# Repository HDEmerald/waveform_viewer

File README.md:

# waveform_viewer
A guitar pedal whose sole purpose is to display the guitar's signal onto a display.

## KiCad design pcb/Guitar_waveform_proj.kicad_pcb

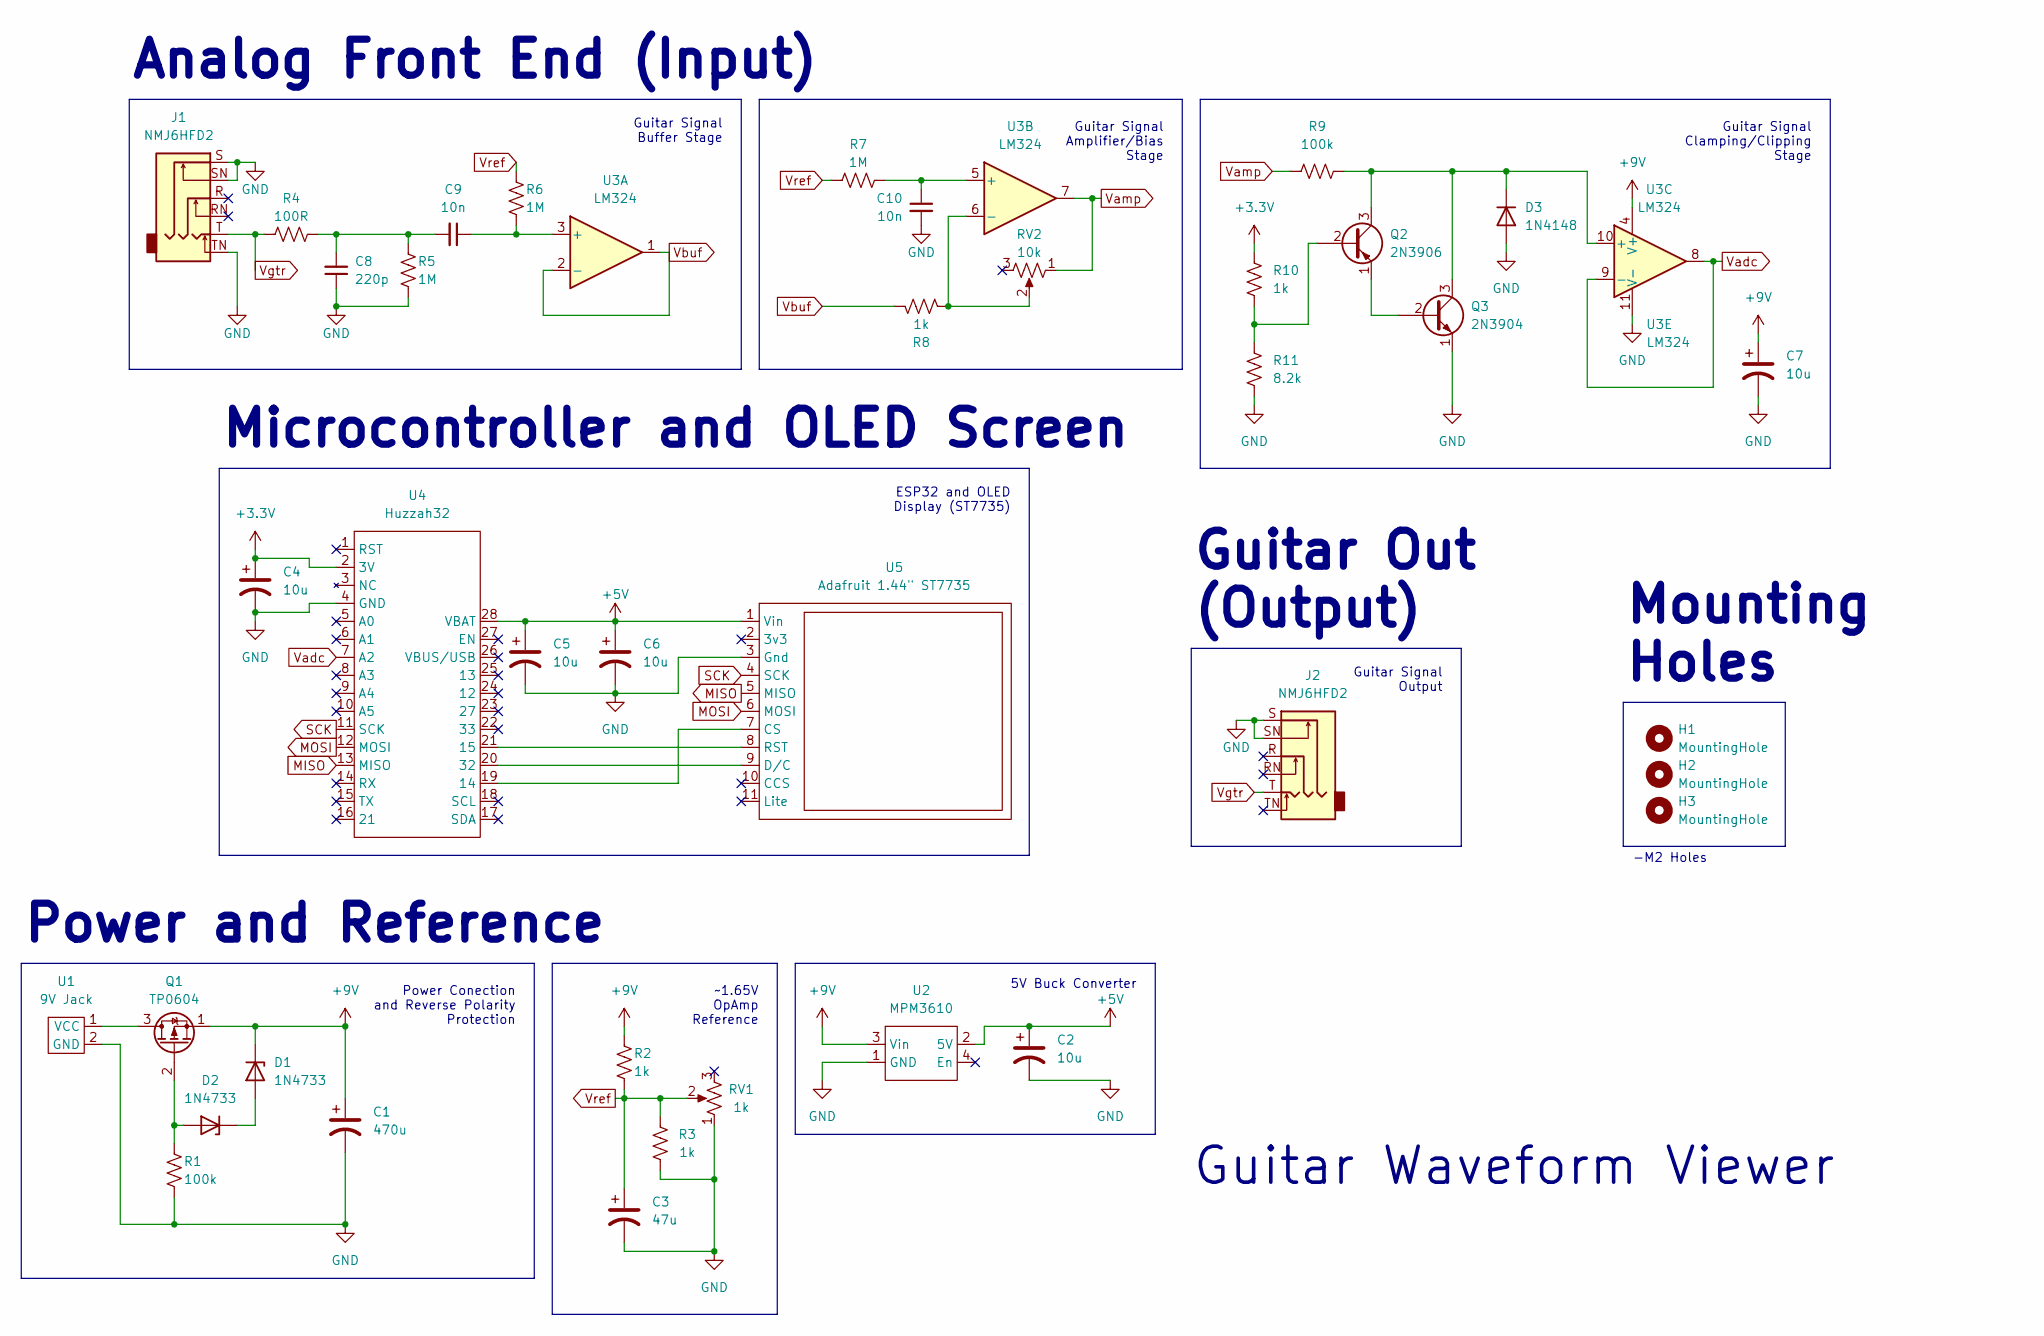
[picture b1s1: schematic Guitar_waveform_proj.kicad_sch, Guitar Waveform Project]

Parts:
C1: 470u; CP_Radial_D8.0mm_P3.50mm
C2, C4, C5, C6, C7: 10u; CP_Radial_D4.0mm_P1.50mm
C3: 47u; CP_Radial_D5.0mm_P2.00mm
C8: 220p; C_Disc_D5.1mm_W3.2mm_P5.00mm
C9, C10: 10n; C_Disc_D5.1mm_W3.2mm_P5.00mm
D1, D2: 1N4733; D_DO-41_SOD81_P7.62mm_Horizontal
D3: 1N4148; D_DO-35_SOD27_P7.62mm_Horizontal
H1, H2, H3: MountingHole; MountingHole_2.2mm_M2
J1, J2: NMJ6HFD2; My Guitar Jack
Q1: TP0604; TO-92_Inline_Wide
Q2: 2N3906; TO-92_Inline_Wide
Q3: 2N3904; TO-92_Inline_Wide
R1, R9: 100k; R_Axial_DIN0207_L6.3mm_D2.5mm_P10.16mm_Horizontal
R2, R3, R8, R10: 1k; R_Axial_DIN0207_L6.3mm_D2.5mm_P10.16mm_Horizontal
R4: 100R; R_Axial_DIN0207_L6.3mm_D2.5mm_P10.16mm_Horizontal
R5, R6, R7: 1M; R_Axial_DIN0207_L6.3mm_D2.5mm_P10.16mm_Horizontal
R11: 8.2k; R_Axial_DIN0207_L6.3mm_D2.5mm_P10.16mm_Horizontal
RV1: 1k; PinHeader_1x03_P2.54mm_Vertical
RV2: 10k; PinHeader_1x03_P2.54mm_Vertical
U1: 9V Jack; PinHeader_1x02_P2.54mm_Vertical
U2: MPM3610; PinHeader_1x04_P2.54mm_Vertical
U3: LM324; DIP-14_W7.62mm_LongPads
U4: Huzzah32; Adafruit_Huzzah32
U5: Adafruit 1.44" ST7735; Adafruit_1.44_ST7735

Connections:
+3.3V: C4.1, R10.1, U4.2 (3V)
+5V: C2.1, C5.1, C6.1, U2.2 (5V), U4.28 (VBAT), U5.1 (Vin)
+9V: C1.1, C7.1, D1.1 (K), Q1.1 (S), R2.1, U2.3 (Vin), U3.4 (V+)
GND: C1.2, C2.2, C3.2, C4.2, C5.2, C6.2, C7.2, C8.1, C10.2, D3.2 (A), J1.S, J1.SN, J1.TN, J2.S, J2.SN, Q3.1 (E), R1.2, R3.2, R5.2, R11.2, RV1.1, U1.2 (GND), U2.1 (GND), U3.11 (V-), U4.4 (GND), U5.3 (Gnd)
MISO: U4.13 (MISO), U5.5 (MISO)
MOSI: U4.12 (MOSI), U5.6 (MOSI)
unnamed: C8.2, C9.2, R4.1, R5.1
unnamed: D1.2 (A), D2.1 (K)
unnamed: D2.2 (A), Q1.2 (G), R1.1
unnamed: D3.1 (K), Q2.3 (C), Q3.3 (C), R9.1, U3.10 (+)
unnamed: Q1.3 (D), U1.1 (VCC)
unnamed: Q2.2 (B), R10.2, R11.1
unnamed: Q2.1 (E), Q3.2 (B)
unnamed: C9.1, R6.2, U3.3 (+)
unnamed: C10.1, R7.1, U3.5 (+)
unnamed: R8.1, RV2.2, U3.6 (-)
unnamed: U4.19 (14), U5.7 (CS)
unnamed: U4.21 (15), U5.8 (RST)
unnamed: U4.20 (32), U5.9 (D/C)
SCK: U4.11 (SCK), U5.4 (SCK)
Vadc: U3.8, U3.9 (-), U4.7 (A2)
Vamp: R9.2, RV2.1, U3.7
Vbuf: R8.2, U3.1, U3.2 (-)
Vgtr: J1.T, J2.T, R4.2
Vref: C3.1, R2.2, R3.1, R6.1, R7.2, RV1.2

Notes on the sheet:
Mounting Holes
Microcontroller and OLED Screen
-M2 Holes
Power and Reference
Guitar Signal Amplifier/Bias Stage
Guitar Waveform Viewer
Guitar Signal Output
5V Buck Converter
Guitar Signal Clamping/Clipping Stage
Analog Front End (Input)
Guitar Signal Buffer Stage
Guitar Out (Output)
~1.65V OpAmp Reference
ESP32 and OLED Display (ST7735)
Power Conection and Reverse Polarity Protection

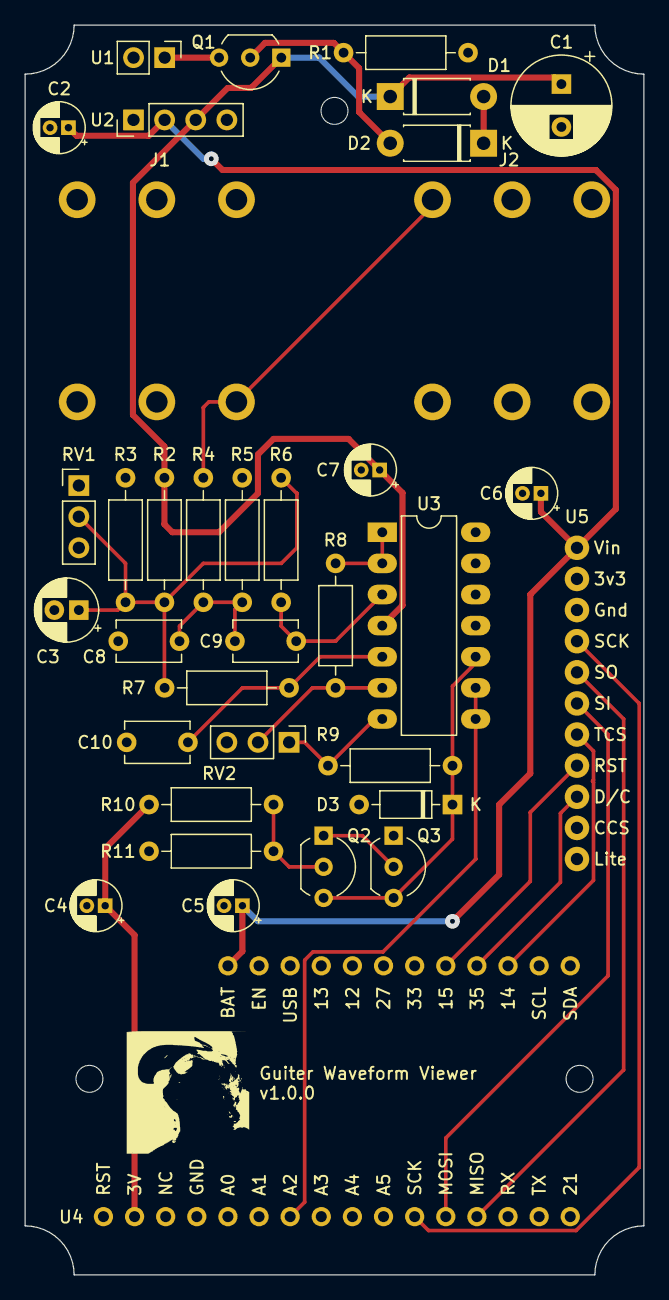
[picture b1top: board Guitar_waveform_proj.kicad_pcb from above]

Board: 2 copper layers, 50.5 x 102.0 mm, 39 parts (0 on the bottom side), 25 nets.

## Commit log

2024-09-06 First complete version
2024-09-06 Added notes directory and v1.0.0 file
2024-09-13 Adding spacer models files
2024-09-13 Added final details about v1.0.0
    Updated the notes,
    updated the pcb files somewhere I think? Nothing major, just touch ups
